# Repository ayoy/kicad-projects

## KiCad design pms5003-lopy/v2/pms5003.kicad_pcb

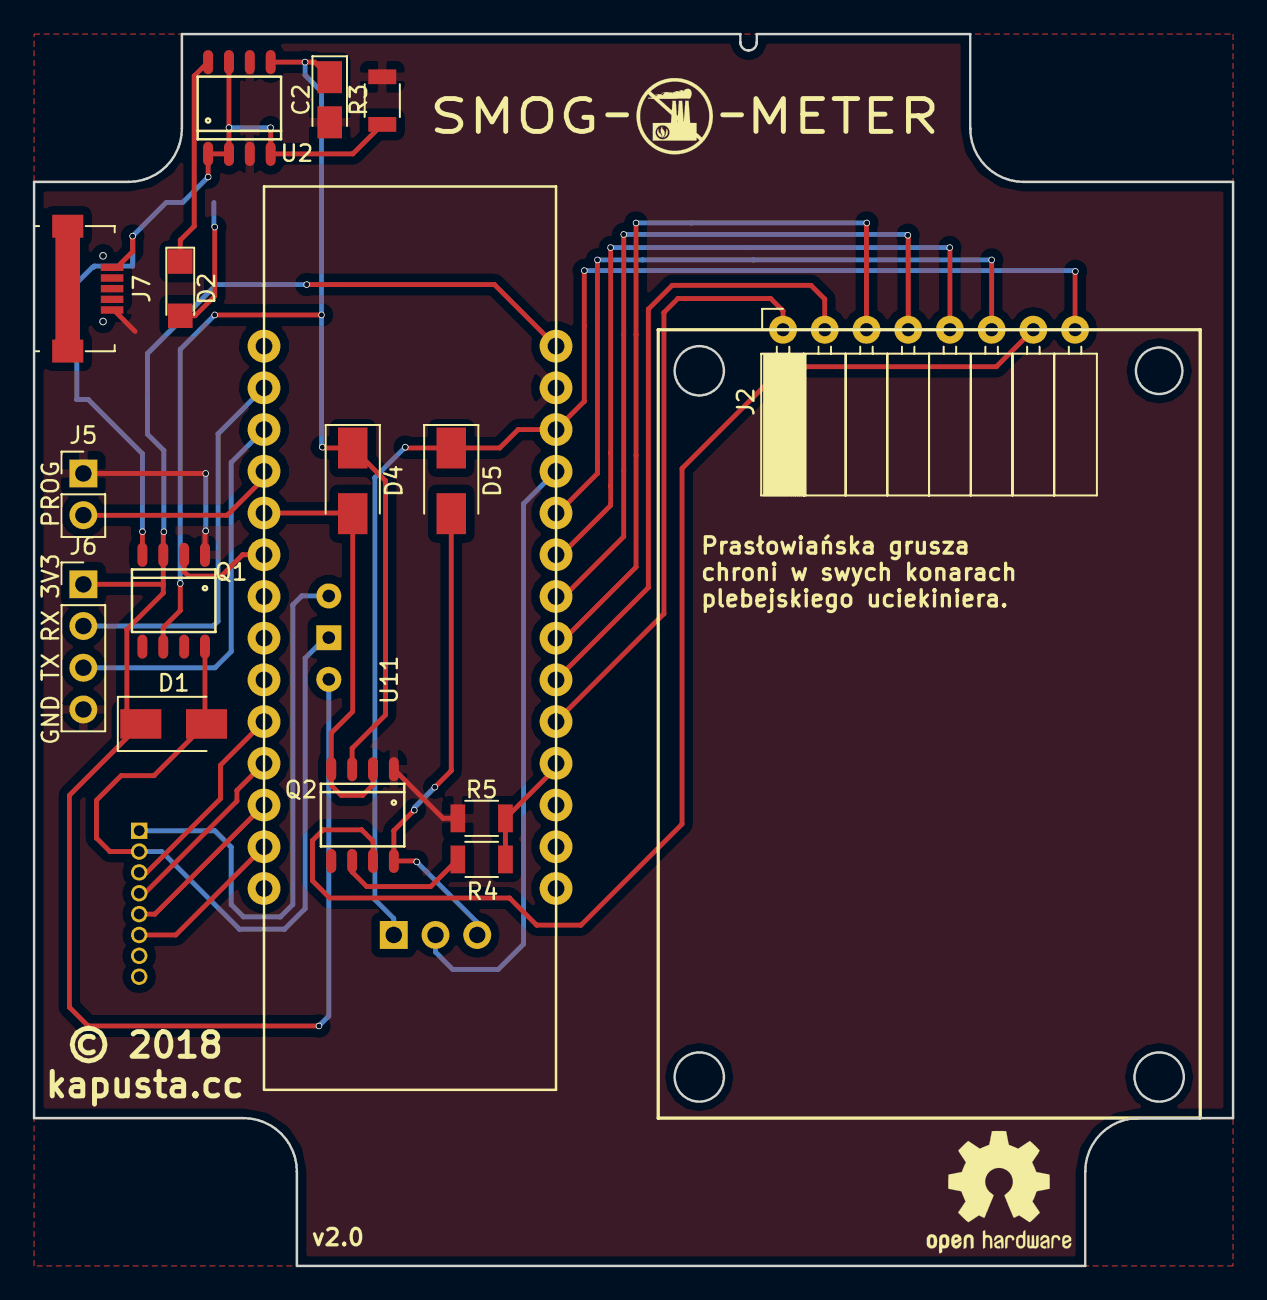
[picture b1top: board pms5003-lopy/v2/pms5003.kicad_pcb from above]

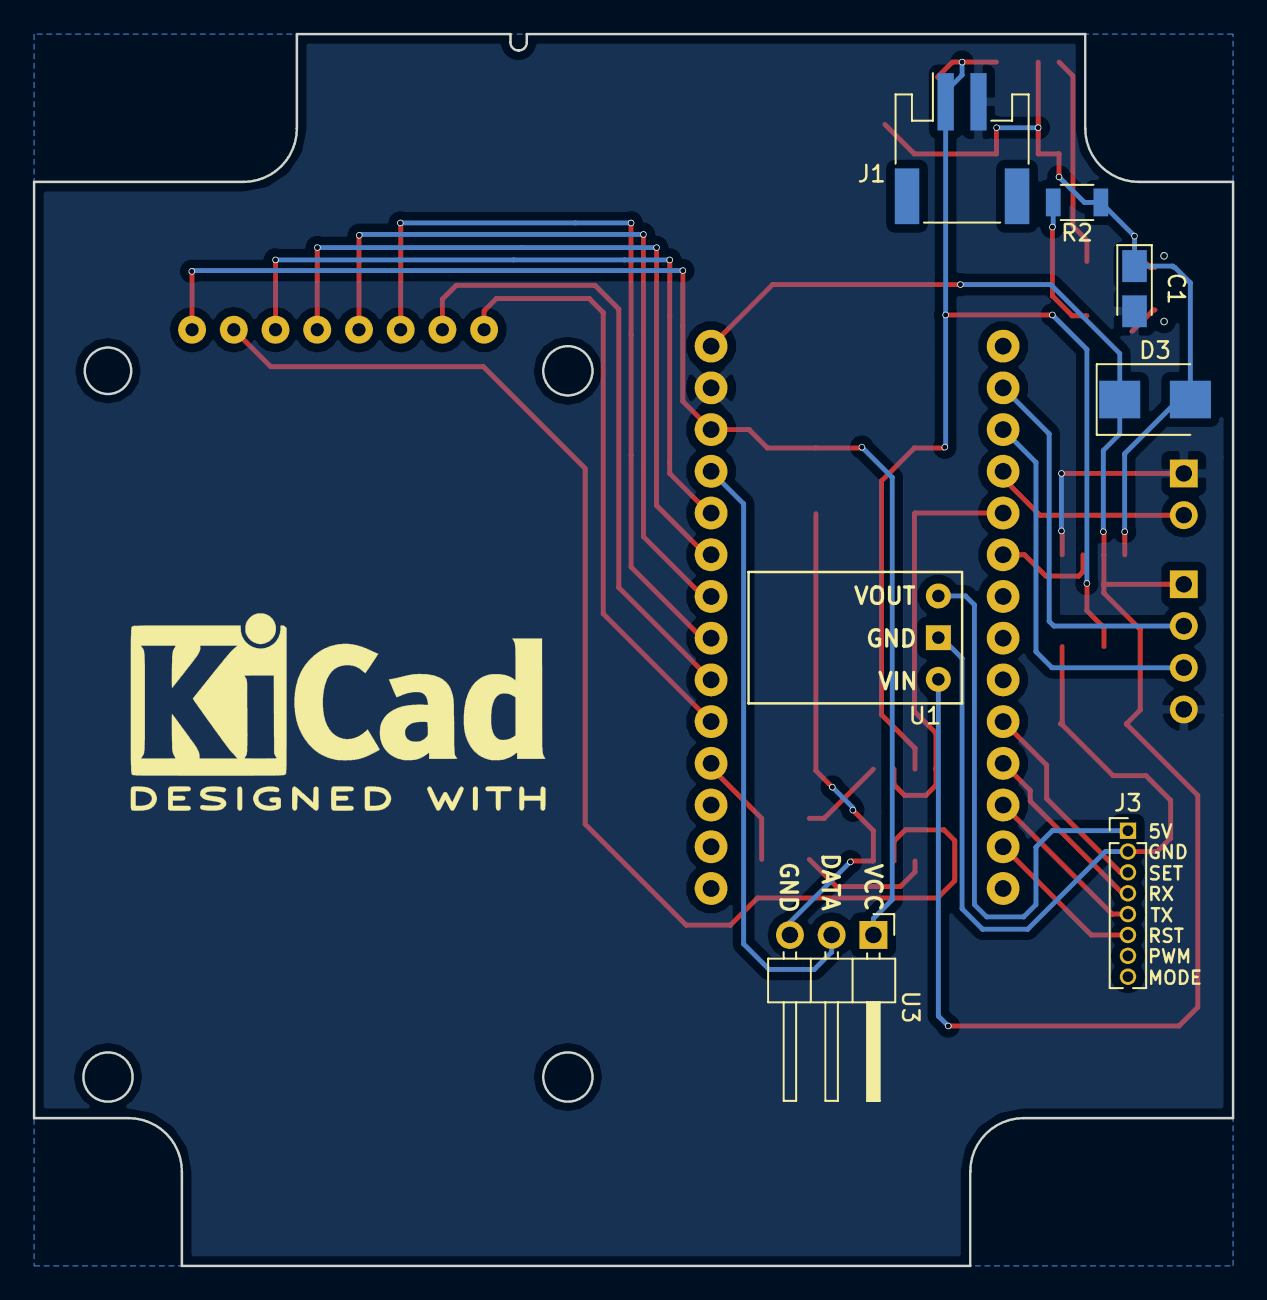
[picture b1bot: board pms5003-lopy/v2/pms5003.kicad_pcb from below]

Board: 2 copper layers, 73.0 x 75.0 mm, 23 parts (7 on the bottom side), 29 nets.

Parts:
C1: 4.7uF; CP_Tantalum_Case-A_EIA-3216-18_Reflow
C2: 10uF; CP_Tantalum_Case-A_EIA-3216-18_Reflow
D1, D4, D5: D; D_SMA
D2: LED; LED_1206
D3: D_Schottky; D_SMB
J1: Battery; JST_PH_S2B-PH-SM4-TB_02x2.00mm_Angled
J2: DISPLAY; Socket_Strip_Angled_1x08_Pitch2.54mm
J3: PMS5003; Pin_Header_Straight_1x08_Pitch1.27mm
J5: P2; Pin_Header_Straight_1x02_Pitch2.54mm
J6: PROG; Pin_Header_Straight_1x04_Pitch2.54mm
J7: USB_OTG; USB_Micro-B_91-US01-517
Q1, Q2: IRF7309IPBF; SO-8
R2: 470; R_1206
R3, R4: 100k; R_1206
R5: 47k; R_1206
U1: U3V12F5; U3V12F9
U2: MAX1811; SO-8
U3: DHT21; Pin_Header_Angled_1x03_Pitch2.54mm
U11: LoPy4; LoPy_with_headers

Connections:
3V3: D5.1, J2.1, U3.1, U11.26
5V: J3.1, U1.3
5V_GND: D1.2, J3.2, Q1.8, U1.2
+USB: C1.1, D3.2, J7.1, Q1.4, R2.1, R3.1, U2.1, U2.2, U2.4, U2.7
-USB: C1.2, C2.2, J1.2, J5.1, J6.4, J7.5, Q1.1, Q2.1, R3.2, R5.2, U2.3, U2.6, U11.27
ADC: R4.2, R5.1, U11.18
ADC_DHT_EN: D4.2, Q2.2, Q2.4, U11.5
BUSY: J2.8, U11.19
CLK: J2.4, U11.23
CS: J2.5, U11.22
DC: J2.6, U11.21
DHT_DATA: U3.2, U11.25
DISP_GND: J2.2, Q2.7
MOSI: J2.3, U11.24
unnamed: D2.1, U2.8
unnamed: D2.2, R2.2
unnamed: D5.2, Q2.8, U3.3
unnamed: J3.3, U11.10
unnamed: J3.4, U11.11
unnamed: J3.5, U11.12
unnamed: J3.6, U11.13
unnamed: Q2.6, R4.1
P2: J5.2, U11.4
PMS_EN: Q1.2, U11.6
RST: J2.7, U11.20
RX: J6.2, U11.2
TX: J6.3, U11.3
VBATT+: C2.1, D4.1, J1.1, Q1.6, Q2.3, U2.5
VCC: D1.1, D3.1, J6.1, Q1.3, U1.1, U11.28

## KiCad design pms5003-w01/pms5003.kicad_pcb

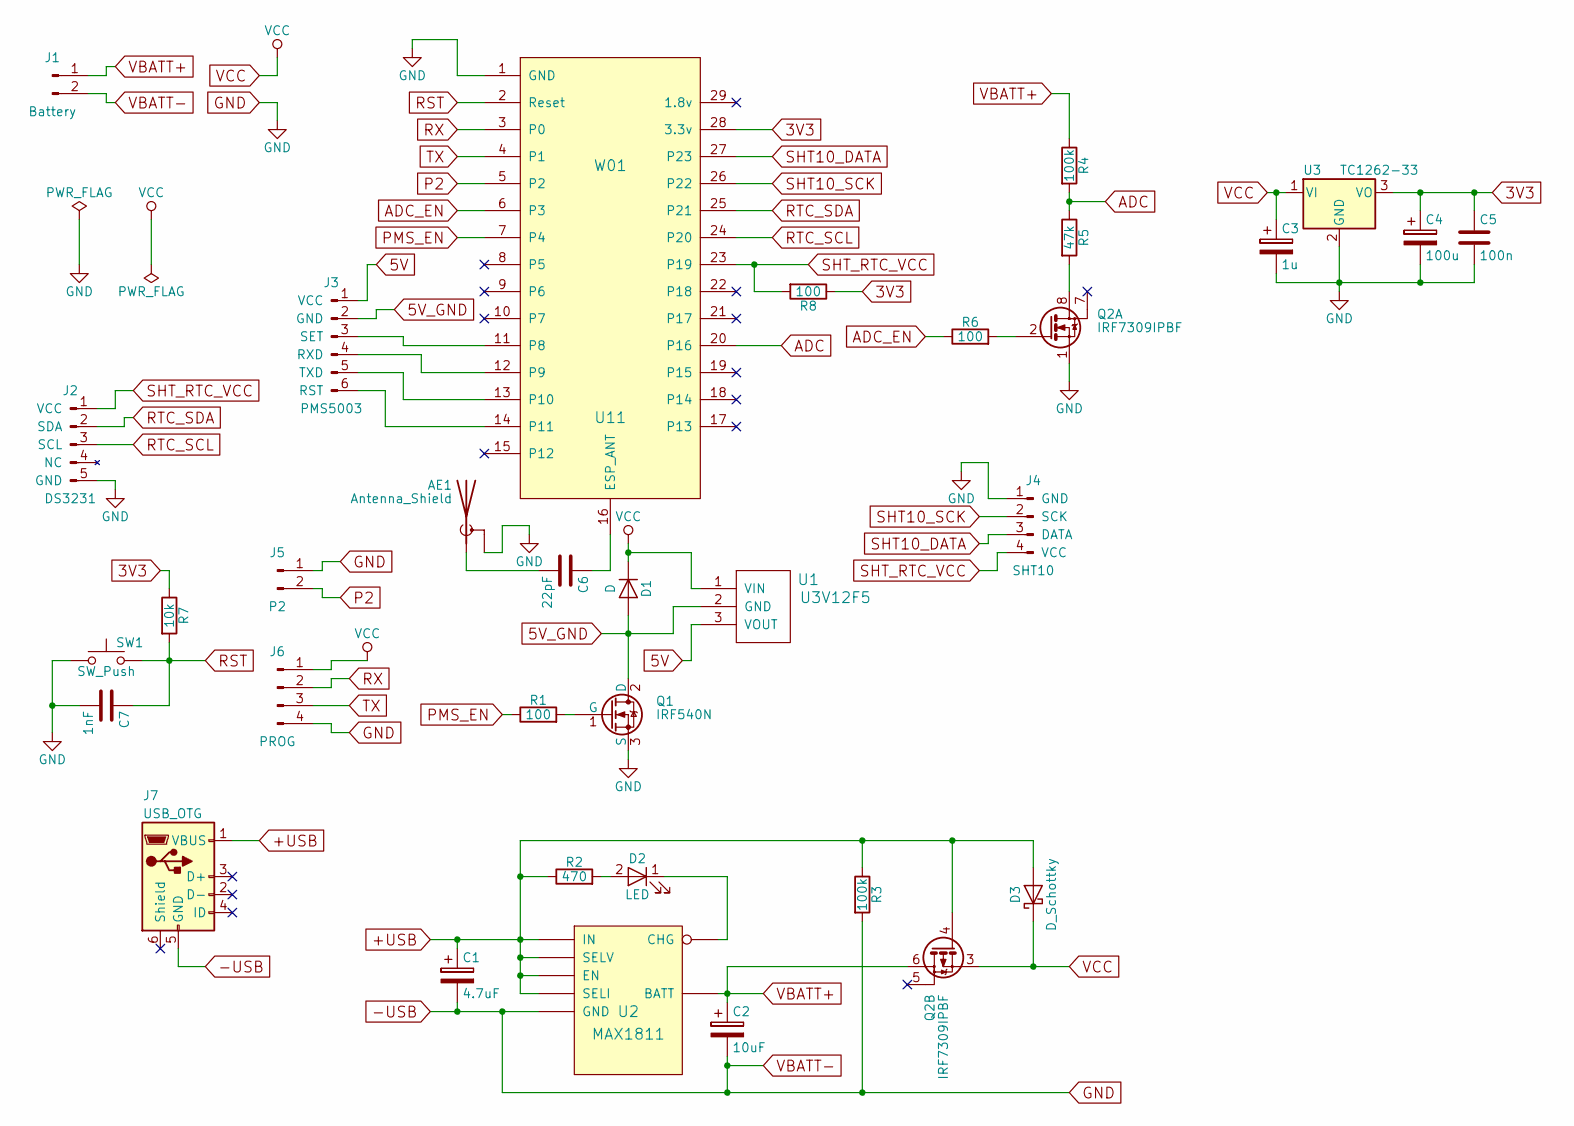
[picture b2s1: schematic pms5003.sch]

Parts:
AE1: Antenna_Shield; U.FL_Molex_MCRF_73412-0110_Vertical; MFG Part Num Value
C1: 4.7uF; CP_Tantalum_Case-A_EIA-3216-18_Reflow
C2: 10uF; CP_Tantalum_Case-A_EIA-3216-18_Reflow
C3: 1u; CP_Tantalum_Case-A_EIA-3216-18_Reflow; MFG Part Num Value
C4: 100u; CP_Elec_6.3x7.7; MFG Part Num Value
C5: 100n; C_1206; MFG Part Num Value
C6: 22pF; C_0805; MFG Part Num Value
C7: 1nF; C_0805; MFG Part Num Value
D1: D; D_SMA
D2: LED; LED_1206
D3: D_Schottky; D_SMA
J1: Battery; JST_PH_S2B-PH-SM4-TB_02x2.00mm_Angled
J2: DS3231; MFG Part Num Value
J3: PMS5003; Socket_Strip_Straight_1x06_Pitch2.54mm; MFG Part Num Value
J4: SHT10; Pin_Header_Straight_1x04_Pitch2.54mm; MFG Part Num Value
J5: P2; Pin_Header_Straight_1x02_Pitch2.54mm; MFG Part Num Value
J6: PROG; Socket_Strip_Straight_1x04_Pitch2.54mm
J7: USB_OTG; USB_Micro-B_91-US01-517; MFG Part Num Value
Q1: IRF540N; SOT-223-3_TabPin2
Q2: IRF7309IPBF; SO-8_5.3x6.2mm_Pitch1.27mm
R1, R6: 100; R_1206
R2: 470; R_1206
R3, R4: 100k; R_1206
R5: 47k; R_1206
R7: 10k; R_1206; MFG Part Num Value
R8: 100
SW1: SW_Push; SW_SPST_B3S-1000; MFG Part Num Value
U1: U3V12F5; U3V12F9
U2: MAX1811; SO-8
U3: TC1262-33; SOT-223-3_TabPin2; MFG Part Num Value
U11: W01; MFG Part Num Value

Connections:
3V3: C4.1, C5.1, R7.1, R8.1, U3.3 (VO), U11.28 (3.3v)
5V: J3.1 (VCC), U1.3 (VOUT)
5V_GND: D1.2 (A), J3.2 (GND), Q1.2 (D), U1.2 (GND)
+USB: C1.1, D3.2 (A), J7.1 (VBUS), Q2.4 (G), R2.1, R3.1, U2.1 (SELV), U2.2 (SELI), U2.4 (IN), U2.7 (EN)
-USB: AE1.2 (Shield), C1.2, C2.2, C3.2, C4.2, C5.2, C7.2, J1.2, J2.5 (GND), J4.1 (GND), J5.1, J6.4, J7.5 (GND), Q1.3 (S), Q2.1 (S), R3.2, SW1.1, U2.3 (GND), U3.2 (GND), U11.1 (GND)
ADC: R4.2, R5.1, U11.20 (P16)
ADC_EN: R6.1, U11.6 (P3)
unnamed: AE1.1 (A), C6.2
unnamed: C6.1, U11.16 (ESP_ANT)
unnamed: D2.1 (K), U2.8 (CHG)
unnamed: D2.2 (A), R2.2
unnamed: J3.3 (SET), U11.11 (P8)
unnamed: J3.4 (RXD), U11.12 (P9)
unnamed: J3.5 (TXD), U11.13 (P10)
unnamed: J3.6 (RST), U11.14 (P11)
unnamed: Q1.1 (G), R1.2
unnamed: Q2.2 (G), R6.2
unnamed: Q2.8 (D), R5.2
P2: J5.2, U11.5 (P2)
PMS_EN: R1.1, U11.7 (P4)
RST: C7.1, R7.2, SW1.2, U11.2 (Reset)
RTC_SCL: J2.3 (SCL), U11.24 (P20)
RTC_SDA: J2.2 (SDA), U11.25 (P21)
RX: J6.2, U11.3 (P0)
SHT10_DATA: J4.3 (DATA), U11.27 (P23)
SHT10_SCK: J4.2 (SCK), U11.26 (P22)
SHT_RTC_VCC: J2.1 (VCC), J4.4 (VCC), R8.2, U11.23 (P19)
TX: J6.3, U11.4 (P1)
VBATT+: C2.1, J1.1, Q2.6 (D), R4.1, U2.5 (BATT)
VCC: C3.1, D1.1 (K), D3.1 (K), J6.1, Q2.3 (1), U1.1 (VIN), U3.1 (VI)

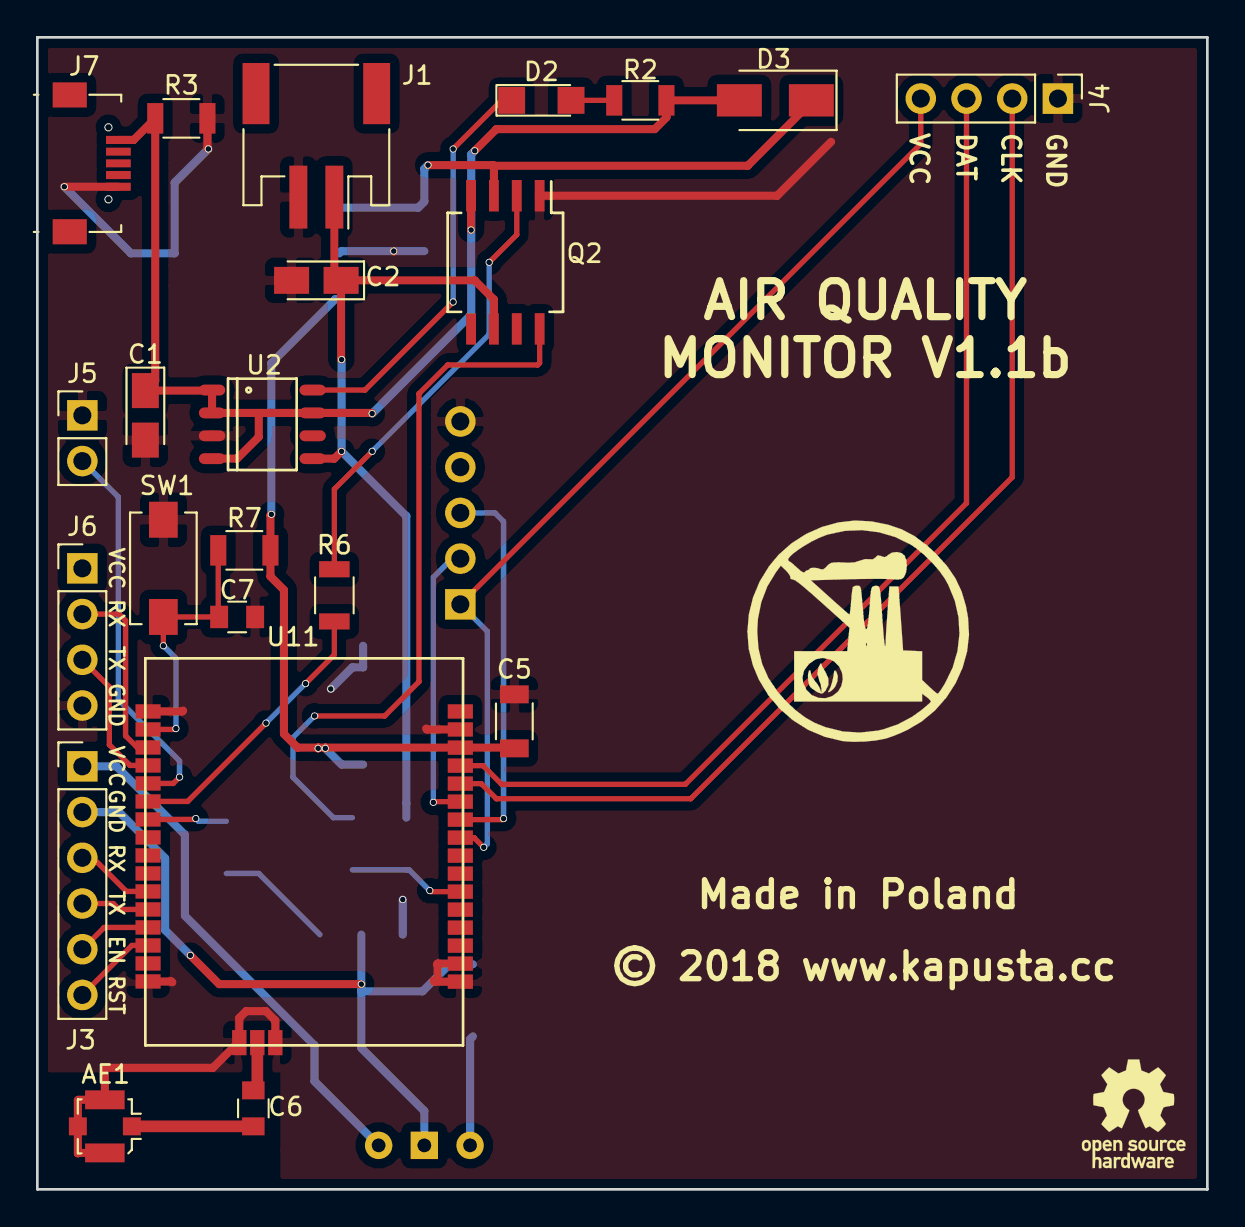
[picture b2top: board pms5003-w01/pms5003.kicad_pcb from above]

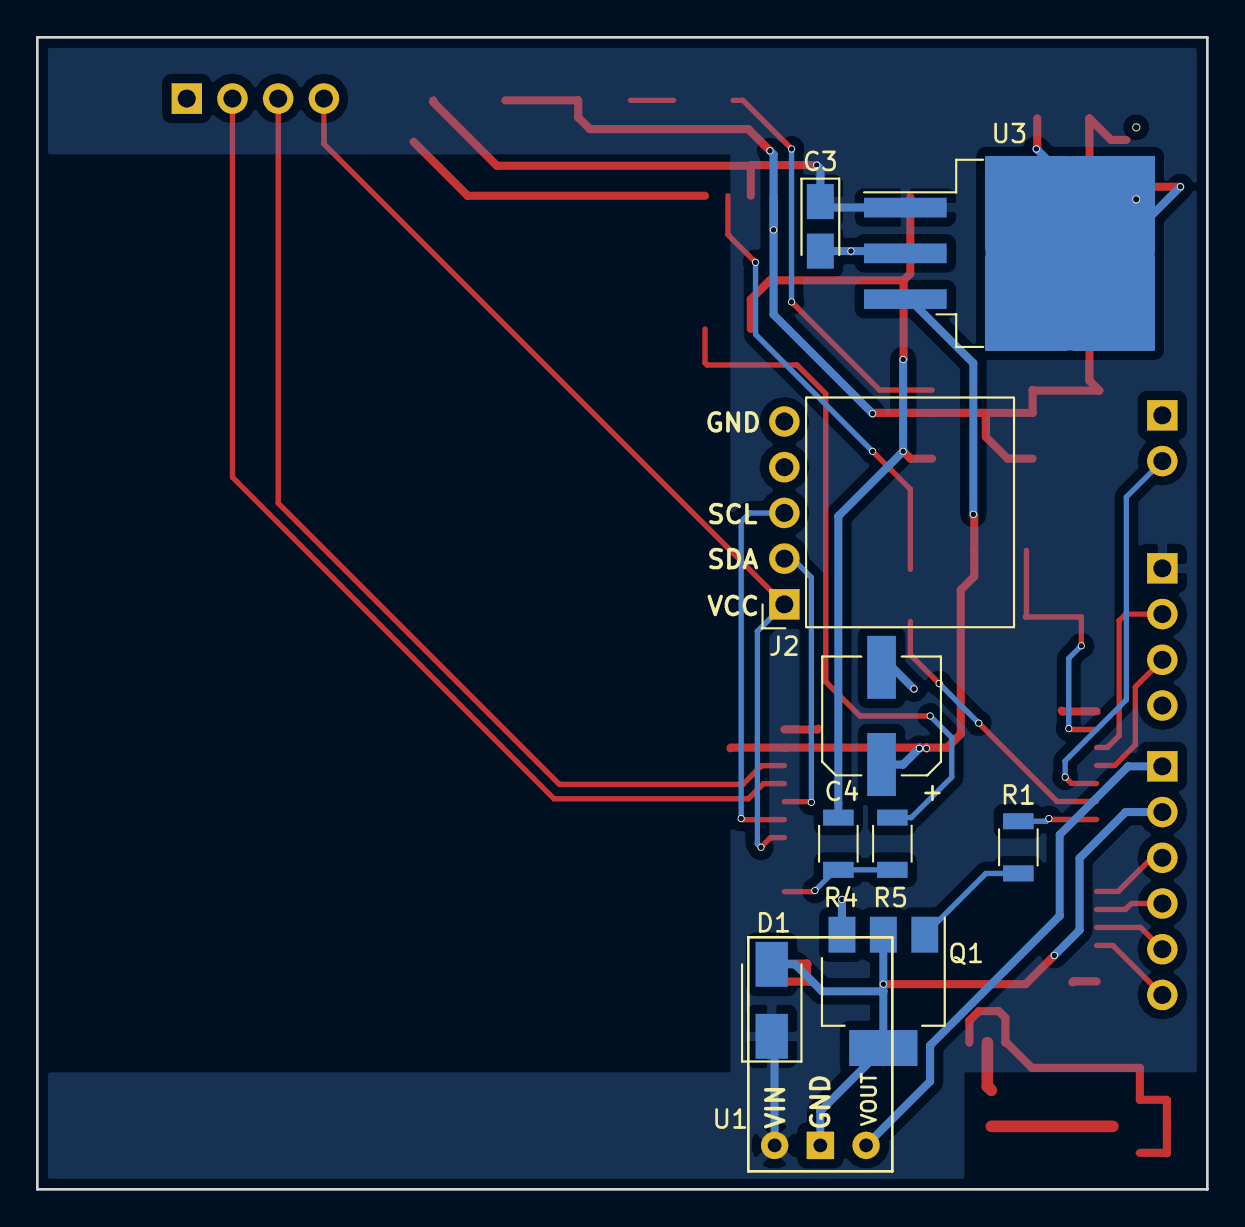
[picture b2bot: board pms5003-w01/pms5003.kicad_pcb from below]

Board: 2 copper layers, 65.0 x 64.0 mm, 32 parts (10 on the bottom side), 30 nets.

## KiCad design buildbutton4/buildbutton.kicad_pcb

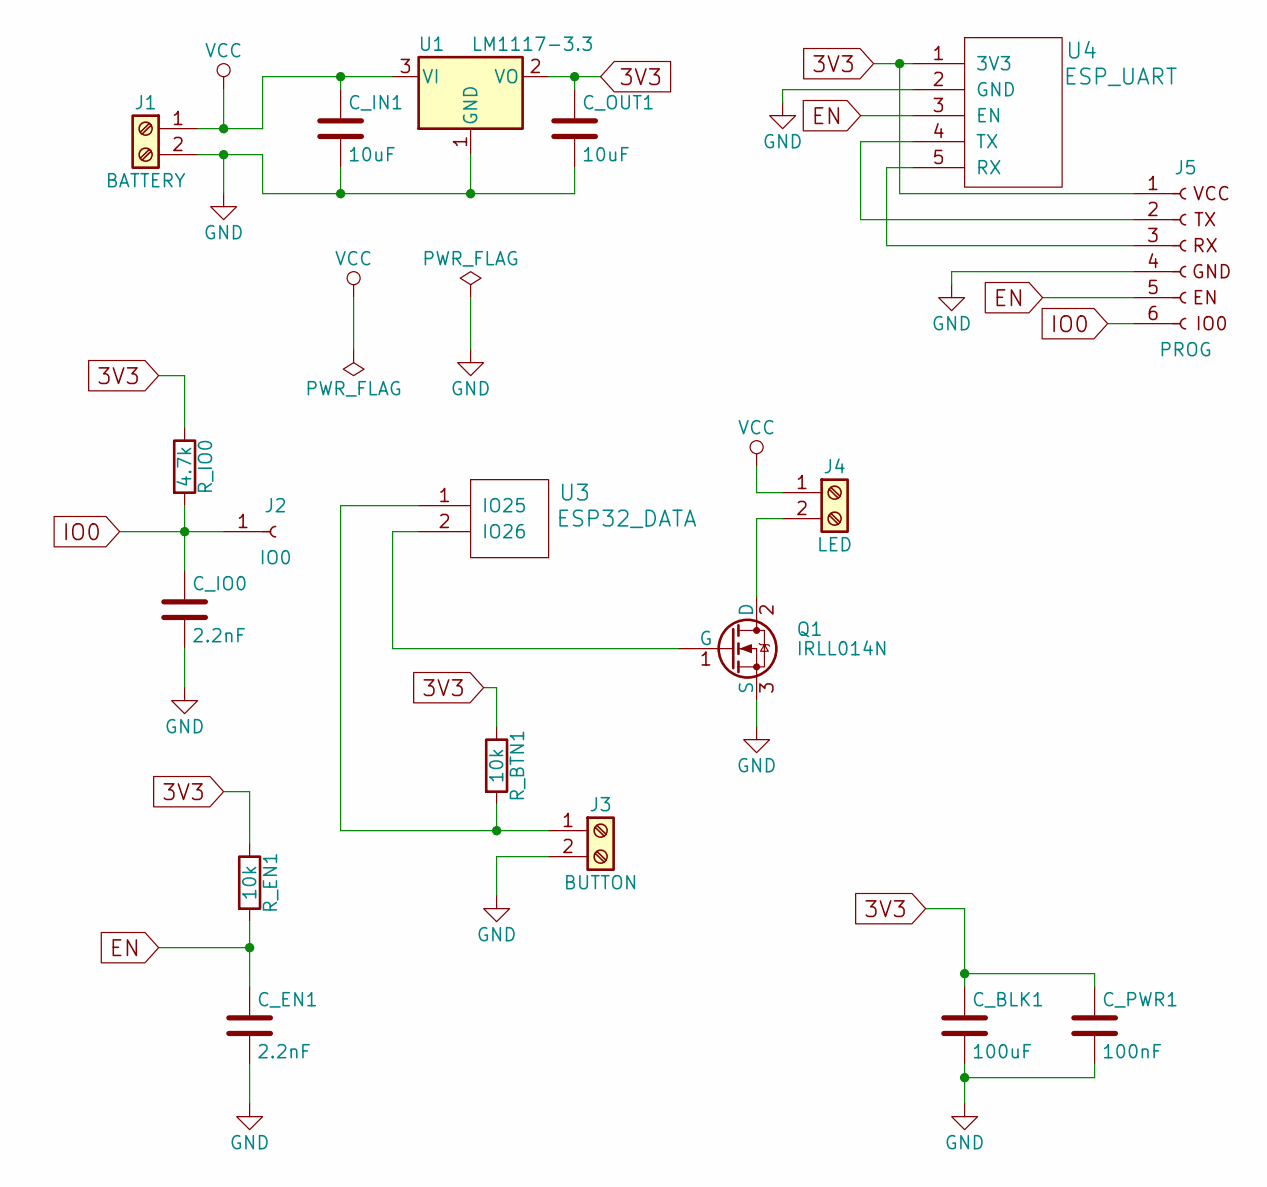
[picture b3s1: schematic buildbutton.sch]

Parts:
C_BLK1: 100uF; CP_Elec_6.3x7.7
C_EN1: 2.2nF; C_1206
C_IN1: 10uF; CP_Tantalum_Case-A_EIA-3216-18_Reflow
C_IO0: 2.2nF; C_1206
C_OUT1: 10uF; CP_Tantalum_Case-A_EIA-3216-18_Reflow
C_PWR1: 100nF; CP_Tantalum_Case-A_EIA-3216-18_Reflow
J1: BATTERY; Socket_Strip_Angled_1x02_Pitch2.54mm
J2: IO0; Socket_Strip_Straight_2x01_Pitch2.54mm
J3: BUTTON; Socket_Strip_Angled_1x02_Pitch2.54mm
J4: LED; Socket_Strip_Angled_1x02_Pitch2.54mm
J5: PROG; Socket_Strip_Angled_1x06_Pitch2.54mm
Q1: IRLL014N; SOT-223
R_BTN1: 10k; R_1206_HandSoldering
R_EN1: 10k; R_1206_HandSoldering
R_IO0: 4.7k; R_1206_HandSoldering
U1: LM1117-3.3; SOT-223
U3: ESP32_DATA; Socket_Strip_Straight_2x01_Pitch2.54mm
U4: ESP_UART; ESP_UART_Socket_Strip

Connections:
3V3: C_BLK1.1, C_OUT1.1, C_PWR1.1, J5.1, R_BTN1.1, R_EN1.1, R_IO0.1, U1.2 (VO), U4.1 (3V3)
EN: C_EN1.1, J5.5, R_EN1.2, U4.3 (EN)
GND: C_BLK1.2, C_EN1.2, C_IN1.2, C_IO0.2, C_OUT1.2, C_PWR1.2, J1.2, J3.2, J5.4, Q1.3 (S), U1.1 (GND), U4.2 (GND)
IO0: C_IO0.1, J2.1, J5.6, R_IO0.2
unnamed: J3.1, R_BTN1.2, U3.1 (IO25)
unnamed: J4.2, Q1.2 (D)
unnamed: J5.2, U4.4 (TX)
unnamed: J5.3, U4.5 (RX)
unnamed: Q1.1 (G), U3.2 (IO26)
VCC: C_IN1.1, J1.1, J4.1, U1.3 (VI)

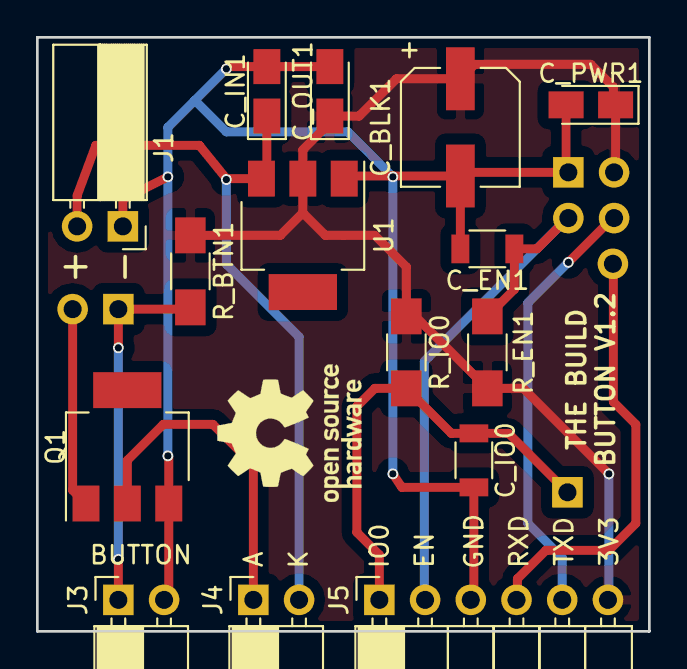
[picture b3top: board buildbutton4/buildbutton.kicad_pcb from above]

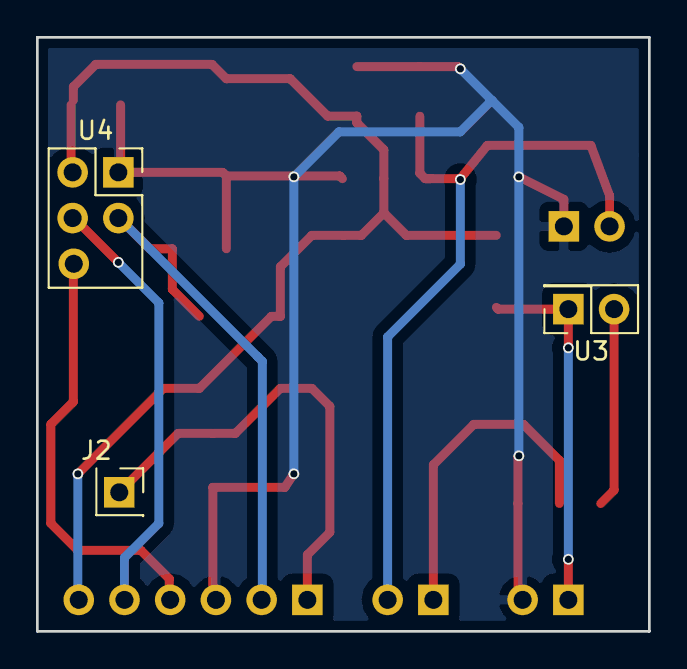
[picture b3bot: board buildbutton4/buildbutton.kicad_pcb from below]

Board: 2 copper layers, 34.0 x 33.0 mm, 18 parts (3 on the bottom side), 10 nets.

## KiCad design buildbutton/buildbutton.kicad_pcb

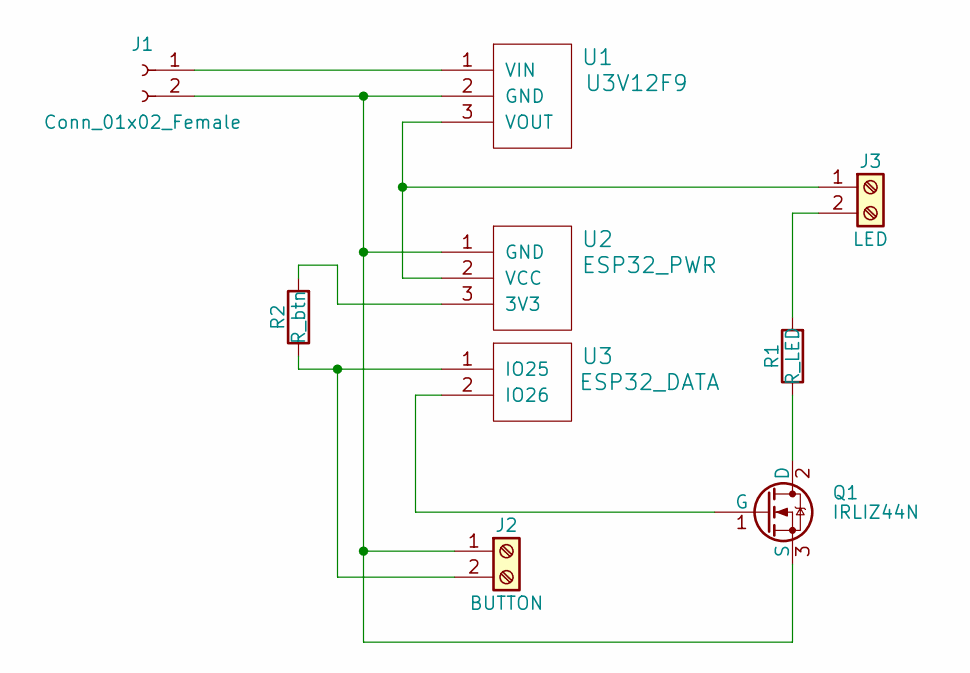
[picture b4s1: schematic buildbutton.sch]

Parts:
J1: Conn_01x02_Female; TerminalBlock_Phoenix_PT-3.5mm_2pol
J2: BUTTON; Socket_Strip_Angled_1x02_Pitch2.54mm
J3: LED; TerminalBlock_Phoenix_PT-3.5mm_2pol
Q1: IRLIZ44N; TO-220-3_Horizontal
R1: R_LED; R_Axial_DIN0204_L3.6mm_D1.6mm_P5.08mm_Horizontal
R2: R_btn; R_Axial_DIN0204_L3.6mm_D1.6mm_P5.08mm_Horizontal
U1: U3V12F9; NCP1402
U2: ESP32_PWR; Socket_Strip_Angled_1x03_Pitch2.54mm
U3: ESP32_DATA; Socket_Strip_Angled_1x02_Pitch2.54mm

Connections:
unnamed: J1.1, U1.1 (VIN)
unnamed: J1.2, J2.1, Q1.3 (S), U1.2 (GND), U2.1 (GND)
unnamed: J2.2, R2.1, U3.1 (IO25)
unnamed: J3.1, U1.3 (VOUT), U2.2 (VCC)
unnamed: J3.2, R1.2
unnamed: Q1.1 (G), U3.2 (IO26)
unnamed: Q1.2 (D), R1.1
unnamed: R2.2, U2.3 (3V3)

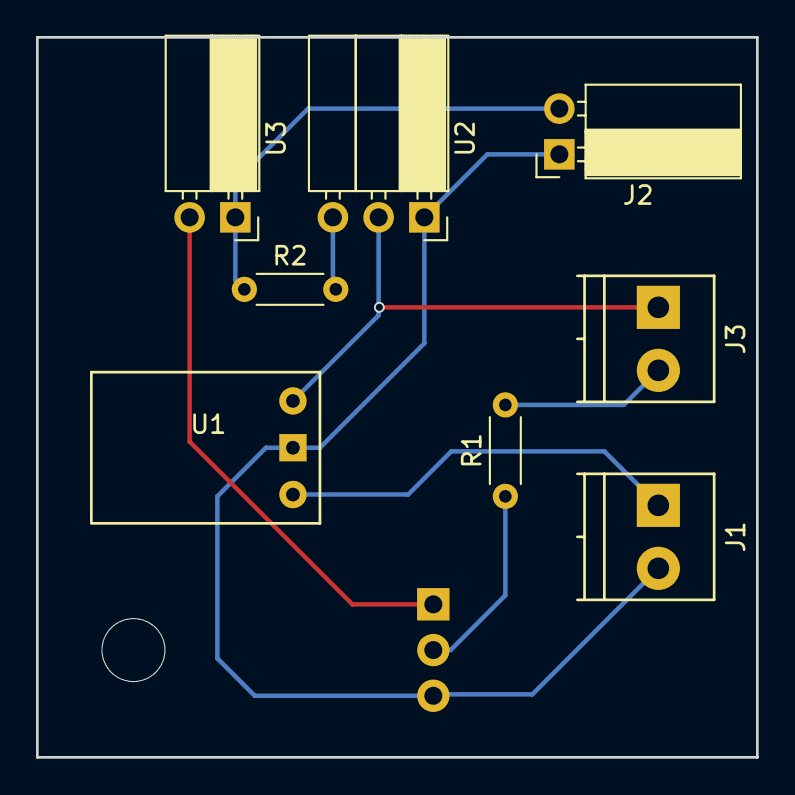
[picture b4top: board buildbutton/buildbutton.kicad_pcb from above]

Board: 2 copper layers, 40.0 x 40.0 mm, 9 parts (1 on the bottom side), 8 nets.

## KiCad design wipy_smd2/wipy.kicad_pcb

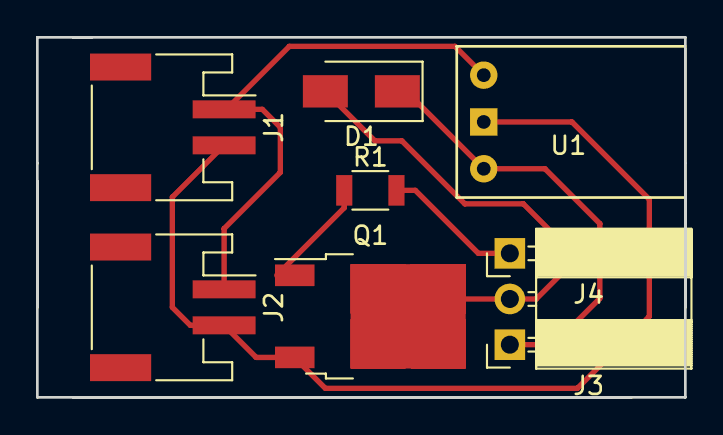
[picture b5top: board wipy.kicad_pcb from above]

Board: 2 copper layers, 36.0 x 20.0 mm, 8 parts (0 on the bottom side), 6 nets.

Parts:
D1: D; D_SMA
J1: LiPo Battery; JST_PH_S2B-PH-SM4-TB_02x2.00mm_Angled
J2: WiPy Power; JST_PH_S2B-PH-SM4-TB_02x2.00mm_Angled
J3: Sensor 5V Power; Socket_Strip_Angled_1x02_Pitch2.54mm
J4: WiPy Sensor Enable Pin; Socket_Strip_Angled_1x01_Pitch2.54mm
Q1: IRLR2905; TO-252-2
R1: R; R_1206
U1: NCP1402

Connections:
+3V8: J1.1, J2.1, U1.1
GND: J1.2, J2.2, Q1.3, U1.2
unnamed: D1.1, J3.1, U1.3
unnamed: D1.2, Q1.2
unnamed: J4.1, R1.2
unnamed: Q1.1, R1.1

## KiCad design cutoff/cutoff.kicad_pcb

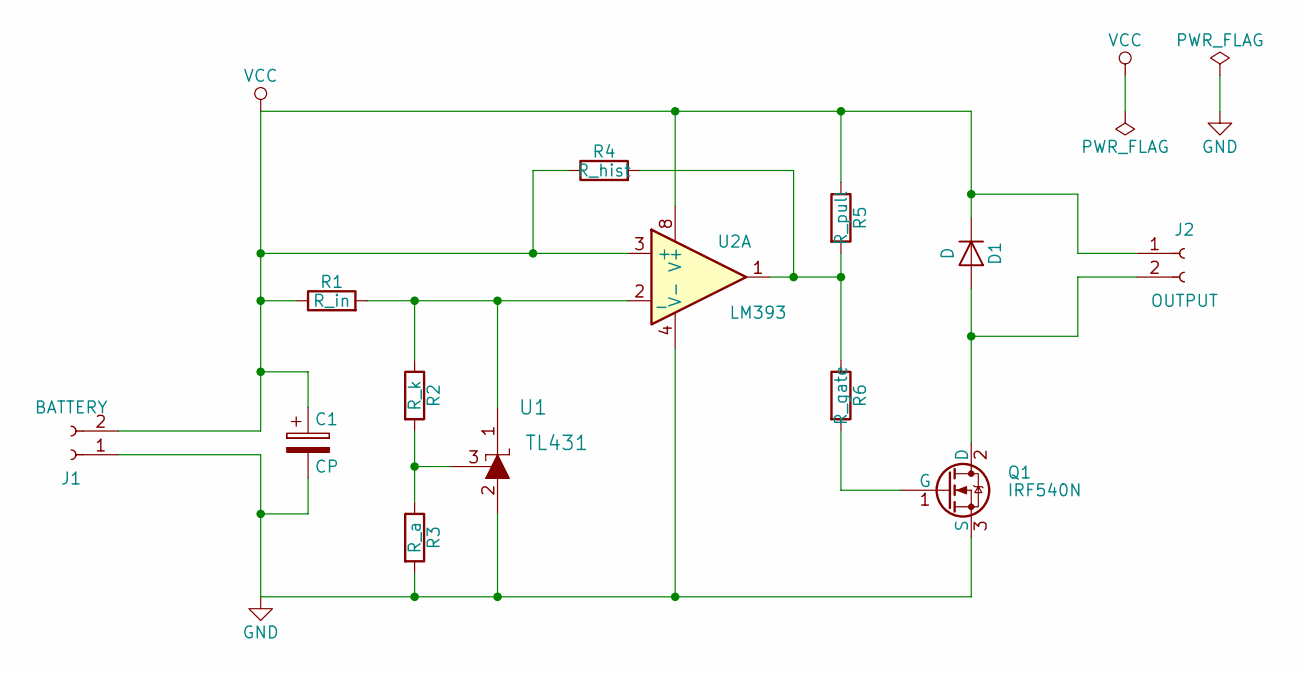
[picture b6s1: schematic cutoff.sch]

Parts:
C1: CP; CP_Radial_D7.5mm_P2.50mm
D1: D; D_A-405_P2.54mm_Vertical_KathodeUp
J1: BATTERY; Socket_Strip_Straight_1x02_Pitch2.54mm
J2: OUTPUT; Socket_Strip_Straight_1x02_Pitch2.54mm
Q1: IRF540N; TO-220-3_Vertical
R1: R_in; R_Axial_DIN0204_L3.6mm_D1.6mm_P2.54mm_Vertical
R2: R_k; R_Axial_DIN0204_L3.6mm_D1.6mm_P2.54mm_Vertical
R3: R_a; R_Axial_DIN0204_L3.6mm_D1.6mm_P2.54mm_Vertical
R4: R_hist; R_Axial_DIN0204_L3.6mm_D1.6mm_P2.54mm_Vertical
R5: R_pull; R_Axial_DIN0204_L3.6mm_D1.6mm_P2.54mm_Vertical
R6: R_gate; R_Axial_DIN0204_L3.6mm_D1.6mm_P2.54mm_Vertical
U1: TL431; TO-92_Inline_Wide
U2: LM393; DIP-8_W7.62mm_Socket

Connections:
GND: C1.2, J1.1, Q1.3 (S), R3.2, U1.2, U2.4 (V-)
unnamed: D1.2 (A), J2.2, Q1.2 (D)
unnamed: Q1.1 (G), R6.2
unnamed: R1.2, R2.1, U1.1, U2.2 (_)
unnamed: R2.2, R3.1, U1.3
unnamed: R4.2, R5.2, R6.1, U2.1
VCC: C1.1, D1.1 (K), J1.2, J2.1, R1.1, R4.1, R5.1, U2.3 (+), U2.8 (V+)

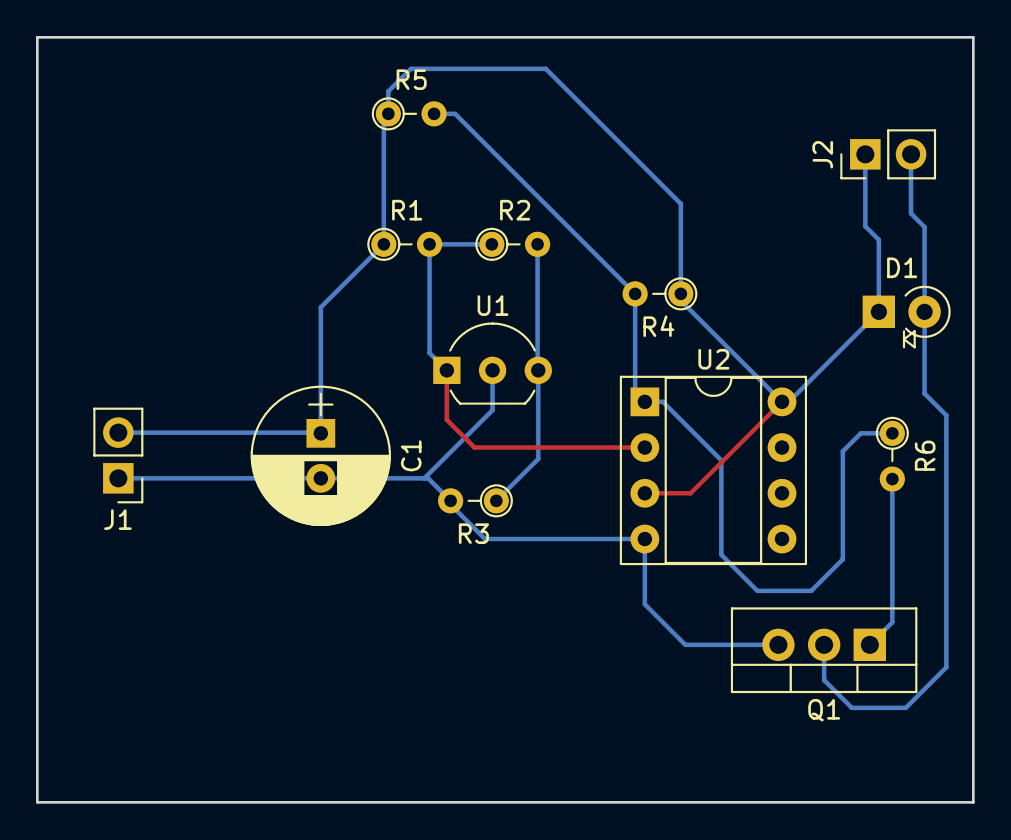
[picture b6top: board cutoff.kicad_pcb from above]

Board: 2 copper layers, 52.0 x 42.5 mm, 13 parts (0 on the bottom side), 7 nets.

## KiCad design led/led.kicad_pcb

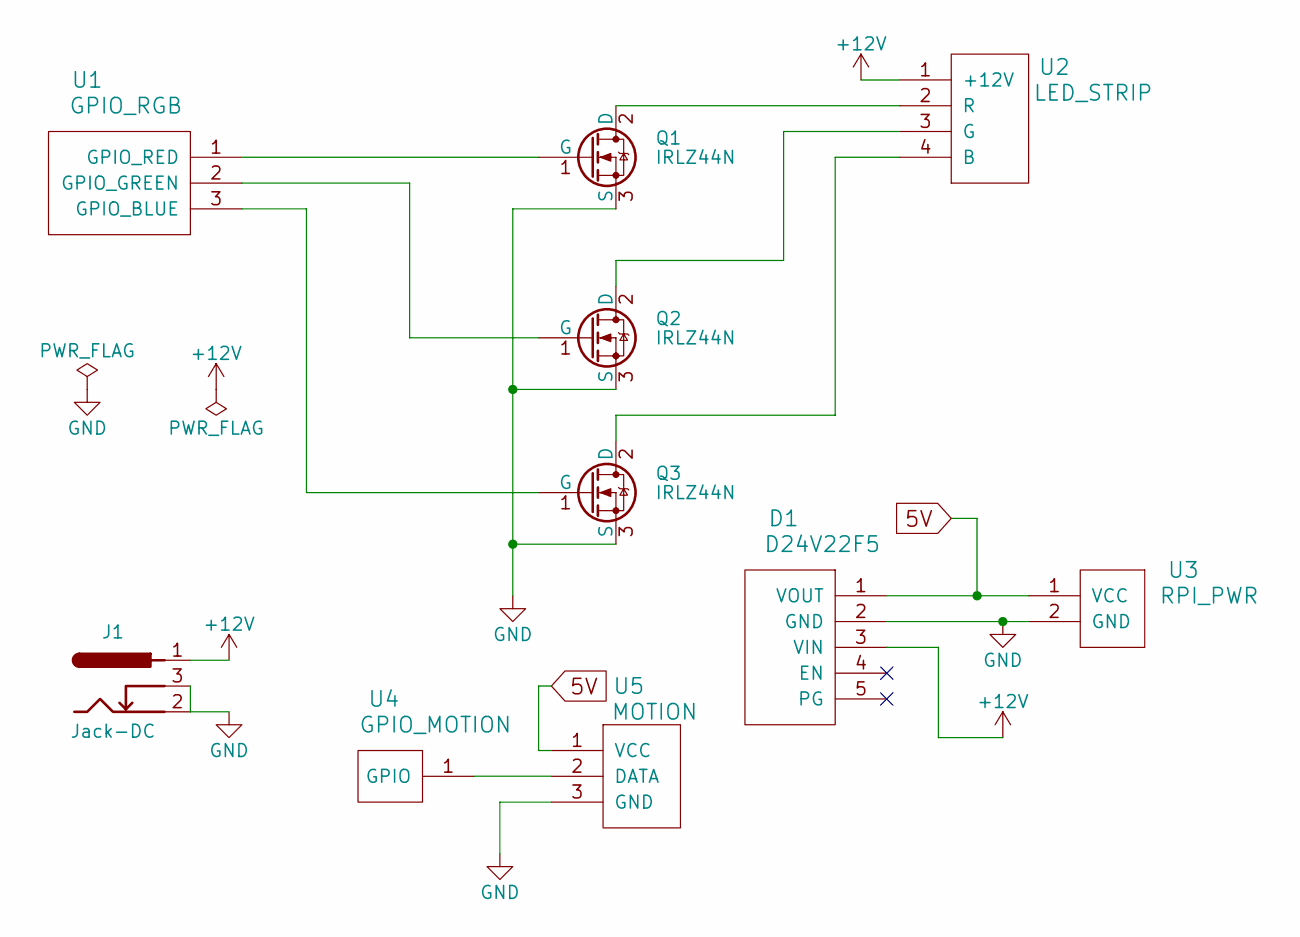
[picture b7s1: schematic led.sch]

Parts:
D1: D24V22F5; Step_down_voltage_regulator
J1: Jack-DC; BARREL_JACK
Q1, Q2, Q3: IRLZ44N; TO-220-3_Horizontal
U1: GPIO_RGB; Socket_Strip_Straight_1x03_Pitch2.54mm
U2: LED_STRIP; Socket_Strip_Angled_1x04_Pitch2.54mm
U3: RPI_PWR; Socket_Strip_Straight_1x02_Pitch2.54mm
U4: GPIO_MOTION; Socket_Strip_Straight_1x01_Pitch2.54mm
U5: MOTION; Socket_Strip_Angled_1x03_Pitch2.54mm

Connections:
5V: D1.1 (VOUT), U3.1 (VCC), U5.1 (VCC)
+12V: D1.3 (VIN), J1.1, U2.1 (+12V)
GND: D1.2 (GND), J1.2, J1.3, Q1.3 (S), Q2.3 (S), Q3.3 (S), U3.2 (GND), U5.3 (GND)
unnamed: Q1.1 (G), U1.1 (GPIO_RED)
unnamed: Q1.2 (D), U2.2 (R)
unnamed: Q2.1 (G), U1.2 (GPIO_GREEN)
unnamed: Q2.2 (D), U2.3 (G)
unnamed: Q3.1 (G), U1.3 (GPIO_BLUE)
unnamed: Q3.2 (D), U2.4 (B)
unnamed: U4.1, U5.2 (DATA)

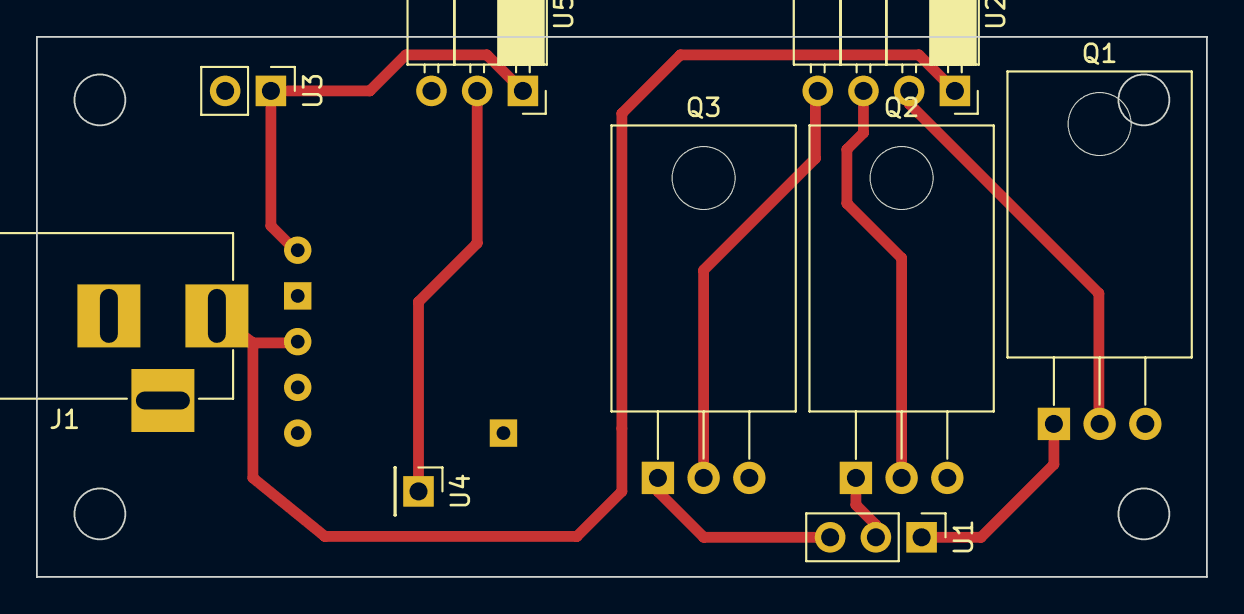
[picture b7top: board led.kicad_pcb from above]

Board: 2 copper layers, 65.0 x 30.0 mm, 10 parts (1 on the bottom side), 10 nets.

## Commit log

2018-01-17 BuildButton v3
2018-01-19 BuildButton v4
2018-01-21 PMS5003 dedicated PCB
2018-01-22 PMS5003: Add battery charger circuit
2018-01-22 Add W01-based PMS5003 board
2018-01-25 PMS5003-lopy: Add VCC pin for SHT10/RTC
2018-01-25 Next iteration of w01 pms5003
2018-01-25 Buildbutton3 update
2018-01-25 PMS5003-lopy with AQ monitor on the board
2018-01-25 Add a pull-up resistor to RTC_VCC
2018-01-25 W01 placement
2018-01-25 Release PMS5003 in two versions
2018-02-02 Update footprint for W01's voltage regulator
2018-03-27 Fix NPMOS in PMS5003
2018-03-27 Move files around
2018-03-31 PMS-lopy v2
2018-04-16 Fixes to v2 PMS5003
2018-10-17 Update to KiCad 5

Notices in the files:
pms5003-lopy/v2/pms5003.kicad_pcb:
© 2018
pms5003-w01/pms5003.kicad_pcb:
© 2018 www.kapusta.cc
